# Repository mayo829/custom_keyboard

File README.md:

# Customized keyboard from scratch!

## Requirements
| Device | Requirement Met | Part number |
| LCD display | 0 |
| knob | 0 |
| [rgb backlit](https://www.digikey.com/en/products/detail/sparkfun-electronics/COM-24837/22321085?gclsrc=aw.ds&gad_source=1&gad_campaignid=20228387720&gbraid=0AAAAADrbLlgSjTrdEqANFxgXgC02mKwfv&gclid=CjwKCAiAjojLBhAlEiwAcjhrDpL0sVmSf_AmglqLysg8uP9_rsrsxjCyNCUdnPwnI6o1eOr4FKzDCRoCRfgQAvD_BwE) | 0 | COM-24837 |
| addressable rgb key lighting | 0 |
| somehow layout the normal 60% plus pgup, pgdn, del, arrows, lcd, and knob and find compatible keycaps (60% keyboard with one extra column) | 0 |
| keycaps need to be, shine-through, square, | 0 |
| case and other stuff to house the keyboard nicely | 0 |
| usbc | 0 |

## BOM
- Mcus:
   - [STM32](https://www.digikey.com/en/products/detail/stmicroelectronics/STM32F072RBT6/4815291s)

- OLED display:
   - [display]()

- Encoder:
   - [encoder](https://www.digikey.com/en/products/detail/bourns-inc/PEC11R-4315K-S0024/7314924)
   - [knob](https://www.digikey.com/en/products/detail/adafruit-industries-llc/5527/16653407?_gl=1*14h9xmt*_up*MQ..*_gs*MQ..&gclid=CjwKCAiA64LLBhBhEiwA-Pxgu-WK6Ms8d8zmGBIC-p0rfidxNpsL_D1lqFmqEvRYpyIKef8caDuRshoCzbMQAvD_BwE&gclsrc=aw.ds&gbraid=0AAAAADrbLljtQo4yarHhxgiW1udqx9cSJ)

- Keycaps
  - [165 key white, grey, red](https://www.aliexpress.us/item/3256803996803052.html?spm=a2g0o.productlist.main.35.295c494elcphuO&algo_pvid=000affab-dda6-4964-b599-618a03716f18&algo_exp_id=000affab-dda6-4964-b599-618a03716f18-34&pdp_ext_f=%7B%22order%22%3A%227%22%2C%22eval%22%3A%221%22%2C%22fromPage%22%3A%22search%22%7D&pdp_npi=6%40dis%21USD%2122.47%2115.73%21%21%2122.47%2115.73%21%402101dedf17680063575245652ec256%2112000053180571953%21sea%21US%217007458592%21X%211%210%21n_tag%3A-29911%3Bd%3Aaca9a7da%3Bm03_new_user%3A-29895&curPageLogUid=Rr0sefmQfAht&utparam-url=scene%3Asearch%7Cquery_from%3A%7Cx_object_id%3A1005004183117804%7C_p_origin_prod%3A)
  - [correct cool colors](https://www.aliexpress.us/item/3256809279540220.html?spm=a2g0o.productlist.main.55.4482ywm5ywm55W&algo_pvid=47f9f85e-3a12-452a-b59a-b0dd7382a6c9&algo_exp_id=47f9f85e-3a12-452a-b59a-b0dd7382a6c9-54&pdp_ext_f=%7B%22order%22%3A%2240%22%2C%22eval%22%3A%221%22%2C%22fromPage%22%3A%22search%22%7D&pdp_npi=6%40dis%21USD%2129.61%2120.73%21%21%21205.47%21143.83%21%402103129f17680065638523771e0064%2112000049189558375%21sea%21US%217007458592%21X%211%210%21n_tag%3A-29911%3Bd%3Aaca9a7da%3Bm03_new_user%3A-29895&curPageLogUid=t9W4kYhWIKt3&utparam-url=scene%3Asearch%7Cquery_from%3A%7Cx_object_id%3A1005009465854972%7C_p_origin_prod%3A)
  
- Switches
  - [Cherry MX2A Silent Red](https://mechanicalkeyboards.com/products/cherry-mx2a-silent-red-45g-linear?variant=48014625145132)

## Resources
- [good guide](https://github.com/ruiqimao/keyboard-pcb-guide)
- [community for keyboard designs](https://kbatelier.org/)
- [reference tutorial](https://www.youtube.com/watch?v=u13yRbBiRYM)

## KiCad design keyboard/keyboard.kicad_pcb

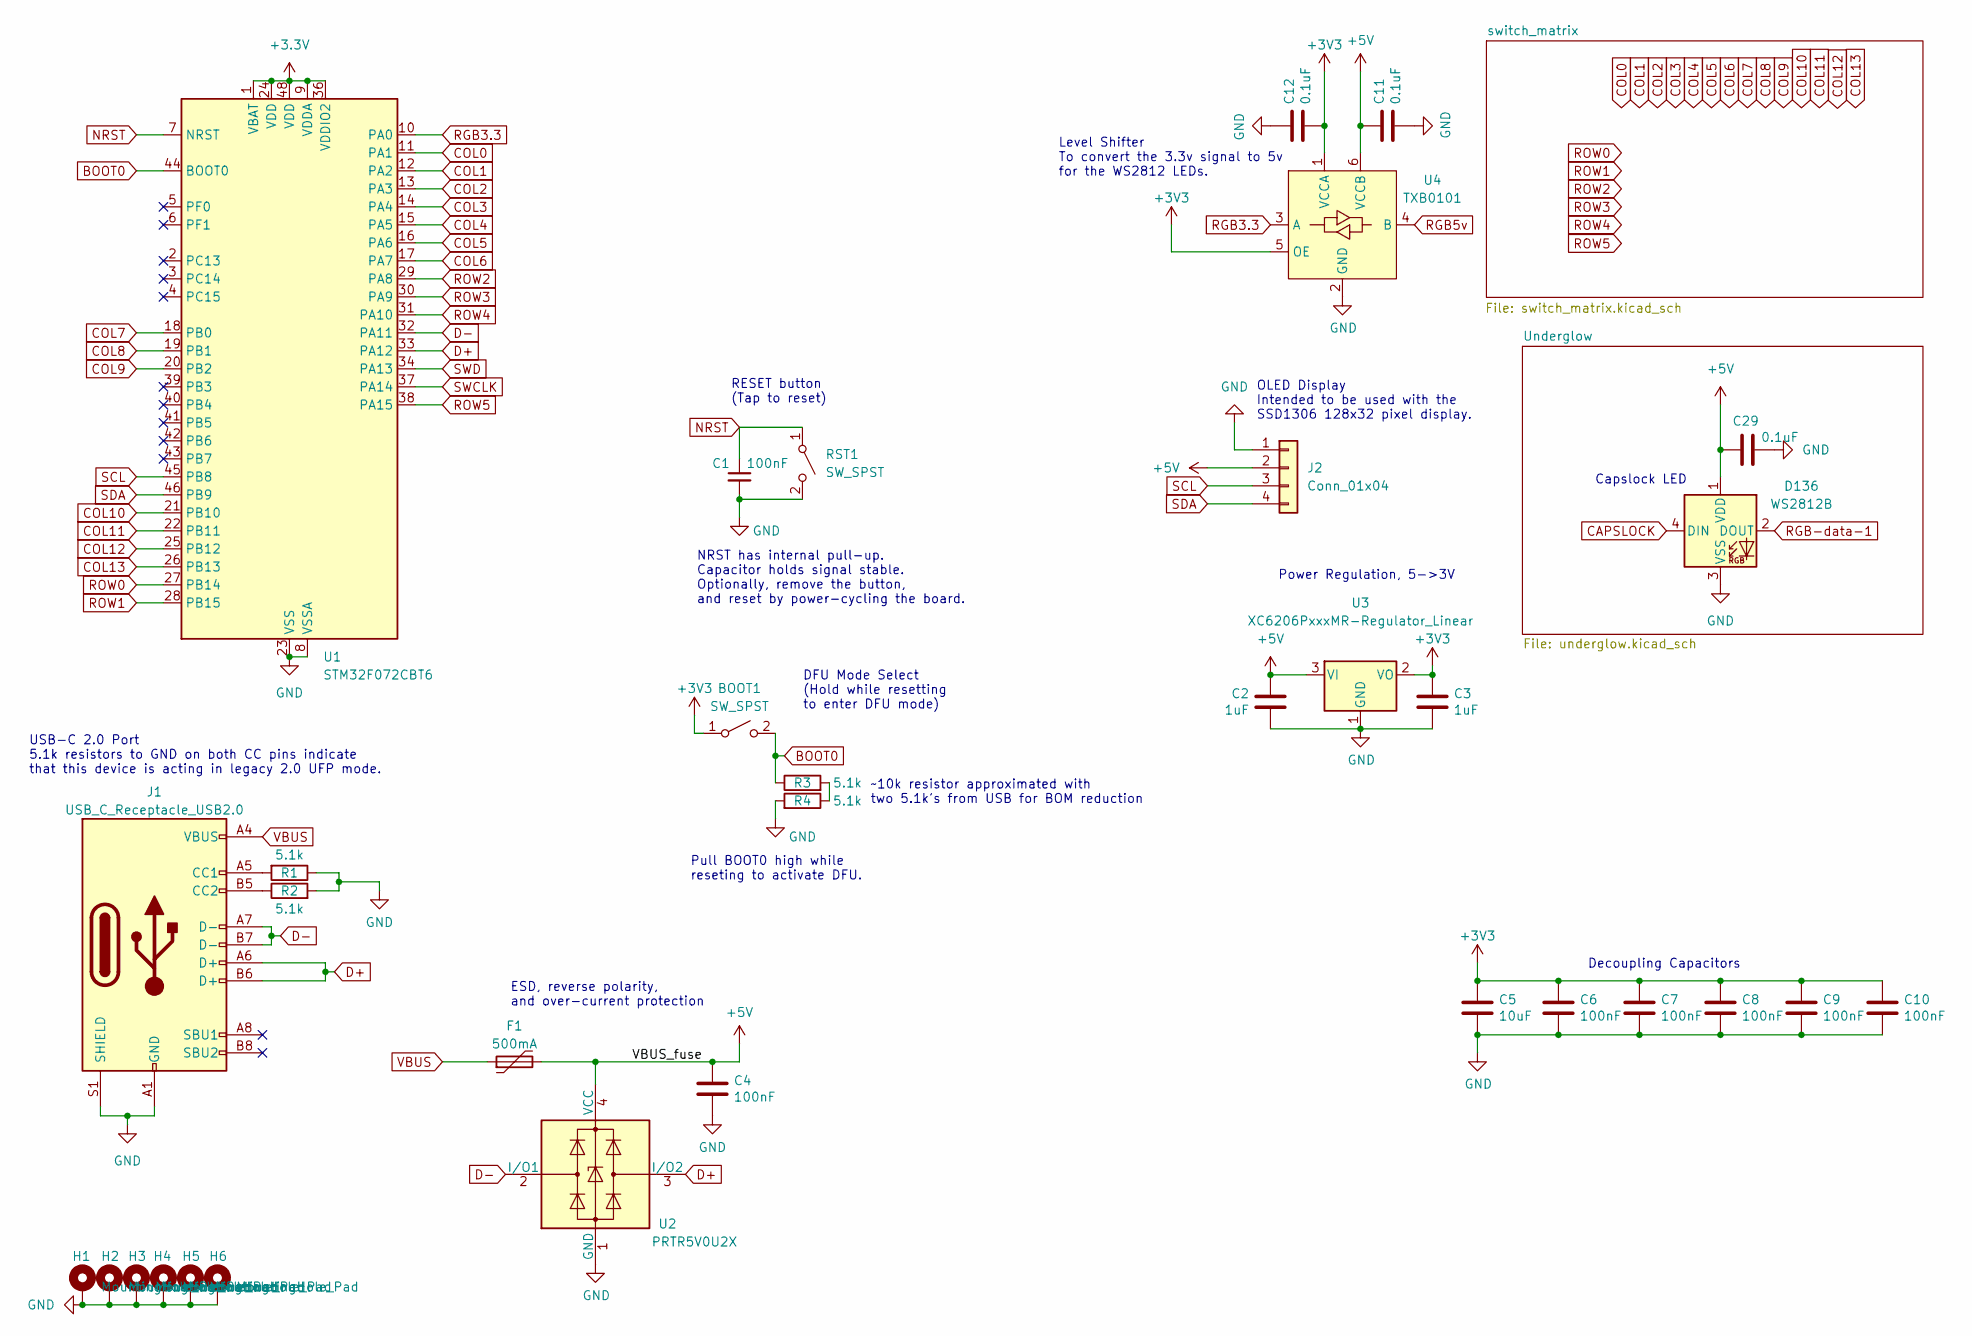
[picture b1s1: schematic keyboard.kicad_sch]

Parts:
BOOT1: SW_SPST; SW_SPST_TL3342
C1, C4, C6, C7, C8, C9, C10: 100nF; C_0402_1005Metric; LCSC C307331
C2, C3: 1uF; C_0402_1005Metric; LCSC C307331
C5: 10uF; C_0603_1608Metric; LCSC C307331
C11, C12: 0.1uF; C_0402_1005Metric; LCSC C307331
C29: 0.1uF; C_0402_1005Metric
D136: WS2812B; LED_WS2812B_PLCC4_5.0x5.0mm_P3.2mm
F1: 500mA; Fuse_1206_3216Metric; LCSC C135341
H1, H2, H3, H4, H5, H6: MountingHole_Pad; MountingHole_3.2mm_M3
J1: USB_C_Receptacle_USB2.0; USB_C_Receptacle_HRO_TYPE-C-31-M-14; JlcRotOffset 180
J2: Conn_01x04; SSD1306-0.91-OLED-4pin-128x32
R1, R2, R3, R4: 5.1k; R_0402_1005Metric
RST1: SW_SPST; SW_SPST_TL3342
U1: STM32F072CBT6; LQFP-48_7x7mm_P0.5mm
U2: PRTR5V0U2X; SOT-143; LCSC C2827688
U3: XC6206PxxxMR-Regulator_Linear; SOT-23; LCSC C5446
U4: TXB0101; SOT-363_SC-70-6_Handsoldering; LCSC C324081

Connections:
+3.3V: U1.1 (VBAT), U1.9 (VDDA), U1.24 (VDD), U1.36 (VDDIO2), U1.48 (VDD)
+3V3: BOOT1.1 (A), C3.1, C5.1, C6.1, C7.1, C8.1, C9.1, C10.1, C12.2, U3.2 (VO), U4.1 (VCCA), U4.5 (OE)
+5V: C2.1, C4.1, C11.1, C29.1, D136.1 (VDD), F1.2, J2.2, U2.4 (VCC), U3.3 (VI), U4.6 (VCCB); also elsewhere on the board
BOOT0: BOOT1.2 (B), R3.1, U1.44 (BOOT0)
CAPSLOCK: D136.4 (DIN); also elsewhere on the board
COL0: U1.11 (PA1); also elsewhere on the board
COL1: U1.12 (PA2); also elsewhere on the board
COL2: U1.13 (PA3); also elsewhere on the board
COL3: U1.14 (PA4); also elsewhere on the board
COL4: U1.15 (PA5); also elsewhere on the board
COL5: U1.16 (PA6); also elsewhere on the board
COL6: U1.17 (PA7); also elsewhere on the board
COL7: U1.18 (PB0); also elsewhere on the board
COL8: U1.19 (PB1); also elsewhere on the board
COL9: U1.20 (PB2); also elsewhere on the board
COL10: U1.21 (PB10); also elsewhere on the board
COL11: U1.22 (PB11); also elsewhere on the board
COL12: U1.25 (PB12); also elsewhere on the board
COL13: U1.26 (PB13); also elsewhere on the board
D+: J1.A6 (D+), J1.B6 (D+), U1.33 (PA12), U2.3 (I/O2)
D-: J1.A7 (D-), J1.B7 (D-), U1.32 (PA11), U2.2 (I/O1)
GND: C1.2, C2.2, C3.2, C4.2, C5.2, C6.2, C7.2, C8.2, C9.2, C10.2, C11.2, C12.1, C29.2, D136.3 (VSS), H1.1, H2.1, H3.1, H4.1, H5.1, H6.1, J1.A1 (GND), J1.A12 (GND), J1.B1 (GND), J1.B12 (GND), J1.S1 (SHIELD), J2.1, R1.1, R2.2, R4.2, RST1.2 (B), U1.8 (VSSA), U1.23 (VSS), U1.35 (VSS), U1.47 (VSS), U2.1 (GND), U3.1 (GND), U4.2 (GND); also elsewhere on the board
NRST: C1.1, RST1.1 (A), U1.7 (NRST)
unnamed: J1.A5 (CC1), R1.2
unnamed: J1.B5 (CC2), R2.1
unnamed: R3.2, R4.1
RGB3.3: U1.10 (PA0), U4.3 (A)
RGB5v: U4.4 (B); also elsewhere on the board
RGB-data-1: D136.2 (DOUT); also elsewhere on the board
ROW0: U1.27 (PB14); also elsewhere on the board
ROW1: U1.28 (PB15); also elsewhere on the board
ROW2: U1.29 (PA8); also elsewhere on the board
ROW3: U1.30 (PA9); also elsewhere on the board
ROW4: U1.31 (PA10); also elsewhere on the board
ROW5: U1.38 (PA15); also elsewhere on the board
SCL: J2.3, U1.45 (PB8)
SDA: J2.4, U1.46 (PB9)
SWCLK: U1.37 (PA14)
SWD: U1.34 (PA13)
VBUS: F1.1, J1.A4 (VBUS), J1.A9 (VBUS), J1.B4 (VBUS), J1.B9 (VBUS)

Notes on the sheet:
Decoupling Capacitors
~10k resistor approximated with two 5.1k's from USB for BOM reduction
RESET button (Tap to reset)
Power Regulation, 5->3V
Pull BOOT0 high while reseting to activate DFU.
Capslock LED
USB-C 2.0 Port 5.1k resistors to GND on both CC pins indicate that this device is acting in legacy 2.0 UFP mode.
NRST has internal pull-up. Capacitor holds signal stable. Optionally, remove the button, and reset by power-cycling the board.
ESD, reverse polarity, and over-current protection
Level Shifter To convert the 3.3v signal to 5v for the WS2812 LEDs.
OLED Display Intended to be used with the SSD1306 128x32 pixel display.
DFU Mode Select (Hold while resetting to enter DFU mode)

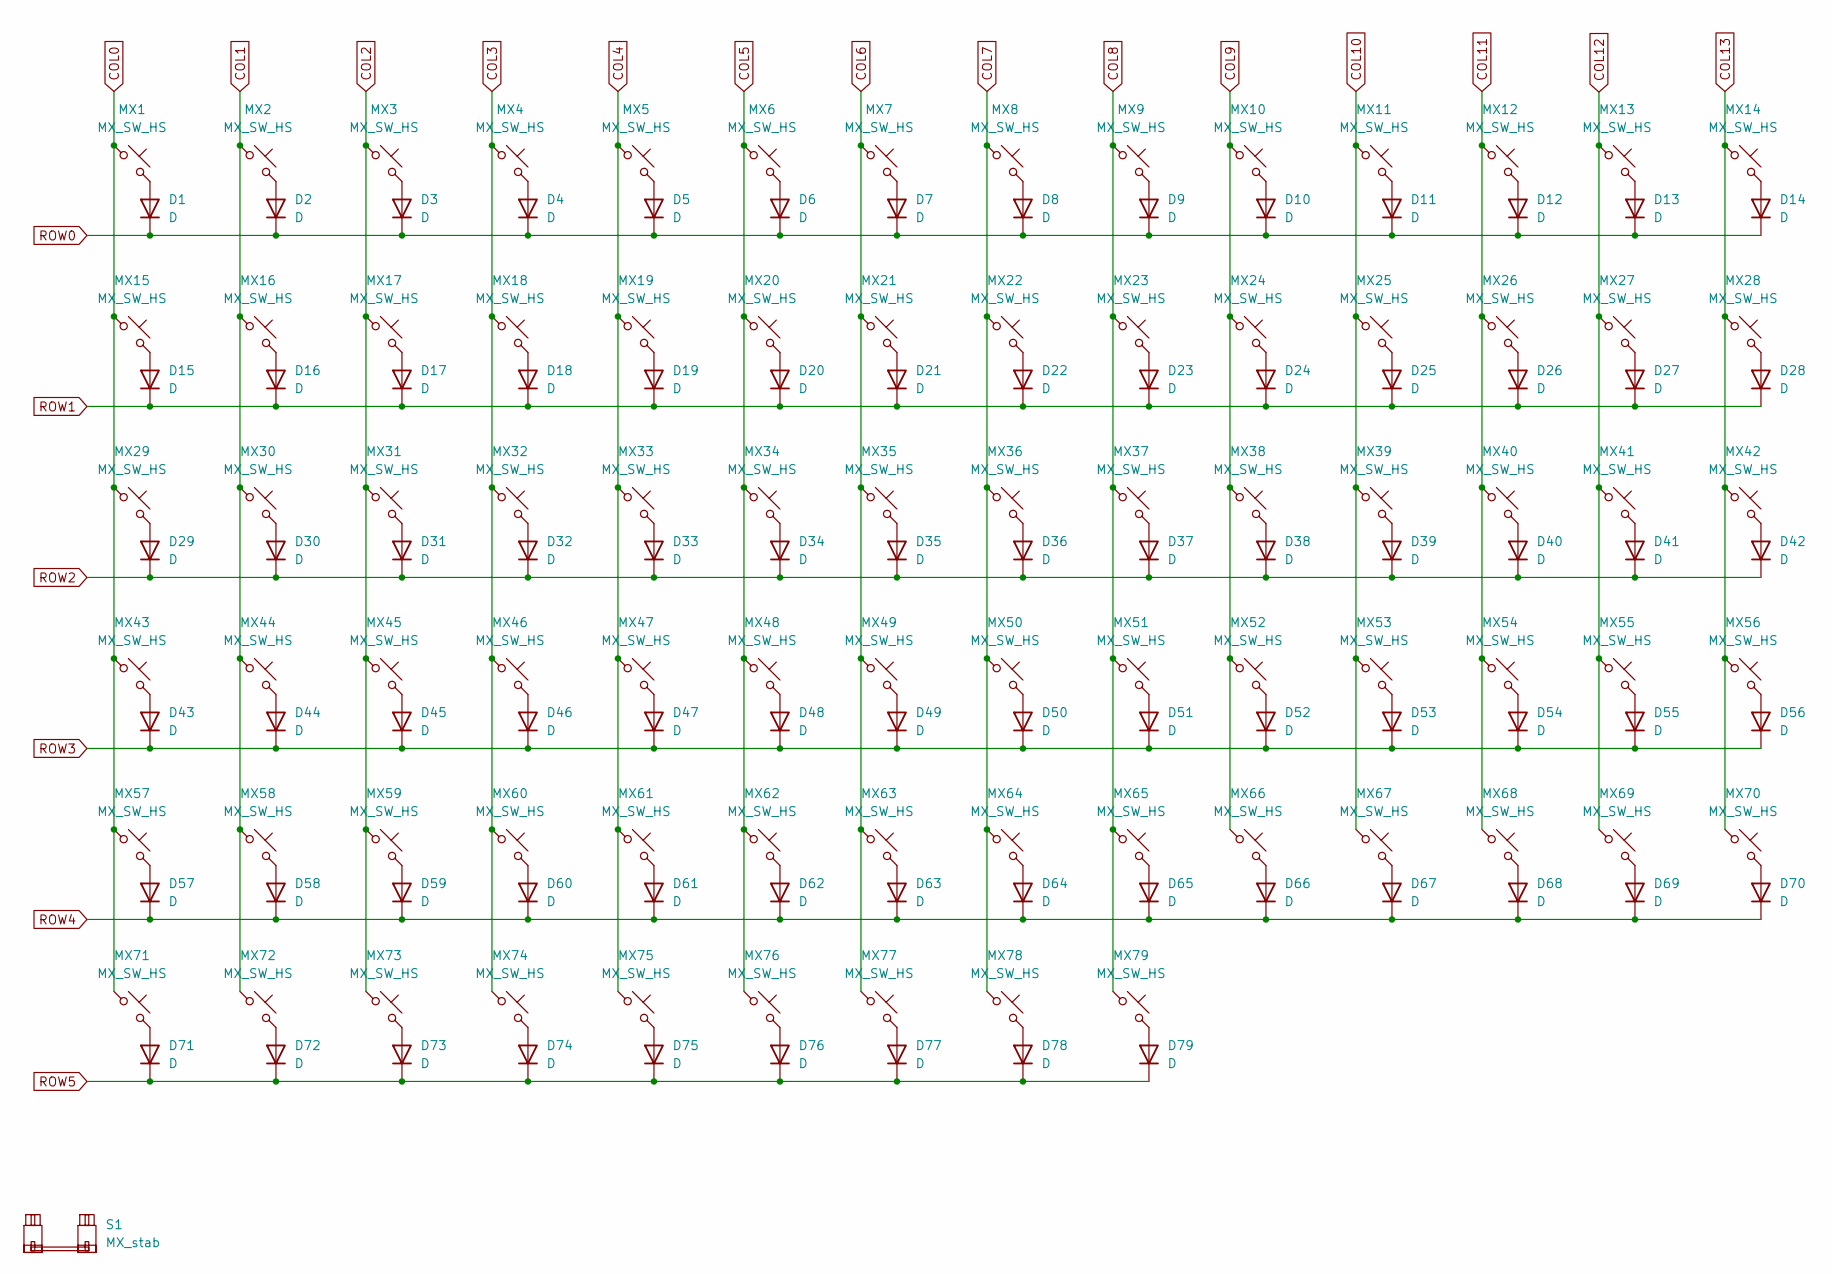
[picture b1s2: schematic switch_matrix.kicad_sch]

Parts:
D1, D2, D3, D4, D5, D6, D7, D8, D9, D10, D11, D12, D13, D14, D15, D16, D17, D18, D19, D20, D21, D22, D23, D24, D25, D26, D27, D28, D29, D30, D31, D32, D33, D34, D35, D36, D37, D38, D39, D40, D41, D42, D43, D44, D45, D46, D47, D48, D49, D50, D51, D52, D53, D54, D55, D56, D57, D58, D59, D60, D61, D62, D63, D64, D65, D66, D67, D68, D69, D70, D71, D72, D73, D74, D75, D76, D77, D78, D79: D; D_SOD-123
MX1, MX2, MX3, MX4, MX5, MX6, MX7, MX8, MX9, MX10, MX11, MX12, MX13, MX14, MX15, MX16, MX17, MX18, MX19, MX20, MX21, MX22, MX23, MX24, MX25, MX26, MX27, MX28, MX29, MX30, MX31, MX32, MX33, MX34, MX35, MX36, MX37, MX38, MX39, MX40, MX41, MX42, MX43, MX44, MX45, MX46, MX47, MX48, MX49, MX50, MX51, MX52, MX53, MX54, MX55, MX56, MX57, MX58, MX59, MX60, MX61, MX62, MX63, MX64, MX65, MX66, MX67, MX68, MX69, MX70, MX71, MX72, MX73, MX74, MX75, MX76, MX77, MX78, MX79: MX_SW_HS; SW_MX_HS_CPG151101S11_1u
S1: MX_stab; STAB_MX_P_6.25u

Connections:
COL0: MX1.1, MX15.1, MX29.1, MX43.1, MX57.1, MX71.1; also elsewhere on the board
COL1: MX2.1, MX16.1, MX30.1, MX44.1, MX58.1, MX72.1; also elsewhere on the board
COL2: MX3.1, MX17.1, MX31.1, MX45.1, MX59.1, MX73.1; also elsewhere on the board
COL3: MX4.1, MX18.1, MX32.1, MX46.1, MX60.1, MX74.1; also elsewhere on the board
COL4: MX5.1, MX19.1, MX33.1, MX47.1, MX61.1, MX75.1; also elsewhere on the board
COL5: MX6.1, MX20.1, MX34.1, MX48.1, MX62.1, MX76.1; also elsewhere on the board
COL6: MX7.1, MX21.1, MX35.1, MX49.1, MX63.1, MX77.1; also elsewhere on the board
COL7: MX8.1, MX22.1, MX36.1, MX50.1, MX64.1, MX78.1; also elsewhere on the board
COL8: MX9.1, MX23.1, MX37.1, MX51.1, MX65.1, MX79.1; also elsewhere on the board
COL9: MX10.1, MX24.1, MX38.1, MX52.1, MX66.1; also elsewhere on the board
COL10: MX11.1, MX25.1, MX39.1, MX53.1, MX67.1; also elsewhere on the board
COL11: MX12.1, MX26.1, MX40.1, MX54.1, MX68.1; also elsewhere on the board
COL12: MX13.1, MX27.1, MX41.1, MX55.1, MX69.1; also elsewhere on the board
COL13: MX14.1, MX28.1, MX42.1, MX56.1, MX70.1; also elsewhere on the board
unnamed: D1.2 (A), MX1.2
unnamed: D2.2 (A), MX2.2
unnamed: D3.2 (A), MX3.2
unnamed: D4.2 (A), MX4.2
unnamed: D5.2 (A), MX5.2
unnamed: D6.2 (A), MX6.2
unnamed: D7.2 (A), MX7.2
unnamed: D8.2 (A), MX8.2
unnamed: D9.2 (A), MX9.2
unnamed: D10.2 (A), MX10.2
unnamed: D11.2 (A), MX11.2
unnamed: D12.2 (A), MX12.2
unnamed: D13.2 (A), MX13.2
unnamed: D14.2 (A), MX14.2
unnamed: D15.2 (A), MX15.2
unnamed: D16.2 (A), MX16.2
unnamed: D17.2 (A), MX17.2
unnamed: D18.2 (A), MX18.2
unnamed: D19.2 (A), MX19.2
unnamed: D20.2 (A), MX20.2
unnamed: D21.2 (A), MX21.2
unnamed: D22.2 (A), MX22.2
unnamed: D23.2 (A), MX23.2
unnamed: D24.2 (A), MX24.2
unnamed: D25.2 (A), MX25.2
unnamed: D26.2 (A), MX26.2
unnamed: D27.2 (A), MX27.2
unnamed: D28.2 (A), MX28.2
unnamed: D29.2 (A), MX29.2
unnamed: D30.2 (A), MX30.2
unnamed: D31.2 (A), MX31.2
unnamed: D32.2 (A), MX32.2
unnamed: D33.2 (A), MX33.2
unnamed: D34.2 (A), MX34.2
unnamed: D35.2 (A), MX35.2
unnamed: D36.2 (A), MX36.2
unnamed: D37.2 (A), MX37.2
unnamed: D38.2 (A), MX38.2
unnamed: D39.2 (A), MX39.2
unnamed: D40.2 (A), MX40.2
unnamed: D41.2 (A), MX41.2
unnamed: D42.2 (A), MX42.2
unnamed: D43.2 (A), MX43.2
unnamed: D44.2 (A), MX44.2
unnamed: D45.2 (A), MX45.2
unnamed: D46.2 (A), MX46.2
unnamed: D47.2 (A), MX47.2
unnamed: D48.2 (A), MX48.2
unnamed: D49.2 (A), MX49.2
unnamed: D50.2 (A), MX50.2
unnamed: D51.2 (A), MX51.2
unnamed: D52.2 (A), MX52.2
unnamed: D53.2 (A), MX53.2
unnamed: D54.2 (A), MX54.2
unnamed: D55.2 (A), MX55.2
unnamed: D56.2 (A), MX56.2
unnamed: D57.2 (A), MX57.2
unnamed: D58.2 (A), MX58.2
unnamed: D59.2 (A), MX59.2
unnamed: D60.2 (A), MX60.2
unnamed: D61.2 (A), MX61.2
unnamed: D62.2 (A), MX62.2
unnamed: D63.2 (A), MX63.2
unnamed: D64.2 (A), MX64.2
unnamed: D65.2 (A), MX65.2
unnamed: D66.2 (A), MX66.2
unnamed: D67.2 (A), MX67.2
unnamed: D68.2 (A), MX68.2
unnamed: D69.2 (A), MX69.2
unnamed: D70.2 (A), MX70.2
unnamed: D71.2 (A), MX71.2
unnamed: D72.2 (A), MX72.2
unnamed: D73.2 (A), MX73.2
unnamed: D74.2 (A), MX74.2
unnamed: D75.2 (A), MX75.2
unnamed: D76.2 (A), MX76.2
unnamed: D77.2 (A), MX77.2
unnamed: D78.2 (A), MX78.2
unnamed: D79.2 (A), MX79.2
ROW0: D1.1 (K), D2.1 (K), D3.1 (K), D4.1 (K), D5.1 (K), D6.1 (K), D7.1 (K), D8.1 (K), D9.1 (K), D10.1 (K), D11.1 (K), D12.1 (K), D13.1 (K), D14.1 (K); also elsewhere on the board
ROW1: D15.1 (K), D16.1 (K), D17.1 (K), D18.1 (K), D19.1 (K), D20.1 (K), D21.1 (K), D22.1 (K), D23.1 (K), D24.1 (K), D25.1 (K), D26.1 (K), D27.1 (K), D28.1 (K); also elsewhere on the board
ROW2: D29.1 (K), D30.1 (K), D31.1 (K), D32.1 (K), D33.1 (K), D34.1 (K), D35.1 (K), D36.1 (K), D37.1 (K), D38.1 (K), D39.1 (K), D40.1 (K), D41.1 (K), D42.1 (K); also elsewhere on the board
ROW3: D43.1 (K), D44.1 (K), D45.1 (K), D46.1 (K), D47.1 (K), D48.1 (K), D49.1 (K), D50.1 (K), D51.1 (K), D52.1 (K), D53.1 (K), D54.1 (K), D55.1 (K), D56.1 (K); also elsewhere on the board
ROW4: D57.1 (K), D58.1 (K), D59.1 (K), D60.1 (K), D61.1 (K), D62.1 (K), D63.1 (K), D64.1 (K), D65.1 (K), D66.1 (K), D67.1 (K), D68.1 (K), D69.1 (K), D70.1 (K); also elsewhere on the board
ROW5: D71.1 (K), D72.1 (K), D73.1 (K), D74.1 (K), D75.1 (K), D76.1 (K), D77.1 (K), D78.1 (K), D79.1 (K); also elsewhere on the board

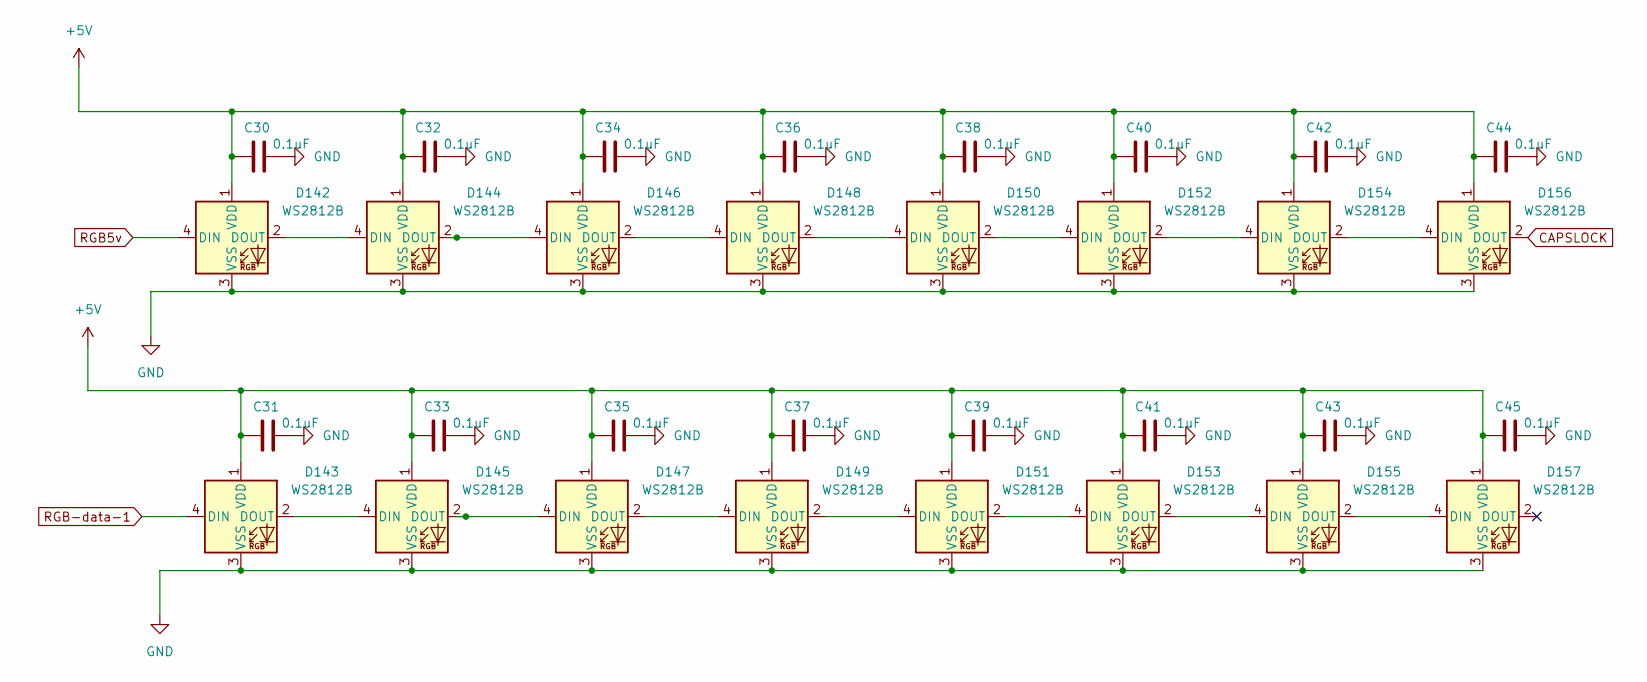
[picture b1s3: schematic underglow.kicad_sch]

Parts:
C30, C31, C32, C33, C34, C35, C36, C37, C38, C39, C40, C41, C42, C43, C44, C45: 0.1uF; C_0402_1005Metric
D142, D143, D144, D145, D146, D147, D148, D149, D150, D151, D152, D153, D154, D155, D156, D157: WS2812B; LED_WS2812B_PLCC4_5.0x5.0mm_P3.2mm

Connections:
+5V: C30.1, C31.1, C32.1, C33.1, C34.1, C35.1, C36.1, C37.1, C38.1, C39.1, C40.1, C41.1, C42.1, C43.1, C44.1, C45.1, D142.1 (VDD), D143.1 (VDD), D144.1 (VDD), D145.1 (VDD), D146.1 (VDD), D147.1 (VDD), D148.1 (VDD), D149.1 (VDD), D150.1 (VDD), D151.1 (VDD), D152.1 (VDD), D153.1 (VDD), D154.1 (VDD), D155.1 (VDD), D156.1 (VDD), D157.1 (VDD); also elsewhere on the board
CAPSLOCK: D156.2 (DOUT); also elsewhere on the board
GND: C30.2, C31.2, C32.2, C33.2, C34.2, C35.2, C36.2, C37.2, C38.2, C39.2, C40.2, C41.2, C42.2, C43.2, C44.2, C45.2, D142.3 (VSS), D143.3 (VSS), D144.3 (VSS), D145.3 (VSS), D146.3 (VSS), D147.3 (VSS), D148.3 (VSS), D149.3 (VSS), D150.3 (VSS), D151.3 (VSS), D152.3 (VSS), D153.3 (VSS), D154.3 (VSS), D155.3 (VSS), D156.3 (VSS), D157.3 (VSS); also elsewhere on the board
unnamed: D142.2 (DOUT), D144.4 (DIN)
unnamed: D143.2 (DOUT), D145.4 (DIN)
unnamed: D144.2 (DOUT), D146.4 (DIN)
unnamed: D145.2 (DOUT), D147.4 (DIN)
unnamed: D146.2 (DOUT), D148.4 (DIN)
unnamed: D147.2 (DOUT), D149.4 (DIN)
unnamed: D148.2 (DOUT), D150.4 (DIN)
unnamed: D149.2 (DOUT), D151.4 (DIN)
unnamed: D150.2 (DOUT), D152.4 (DIN)
unnamed: D151.2 (DOUT), D153.4 (DIN)
unnamed: D152.2 (DOUT), D154.4 (DIN)
unnamed: D153.2 (DOUT), D155.4 (DIN)
unnamed: D154.2 (DOUT), D156.4 (DIN)
unnamed: D155.2 (DOUT), D157.4 (DIN)
RGB5v: D142.4 (DIN); also elsewhere on the board
RGB-data-1: D143.4 (DIN); also elsewhere on the board

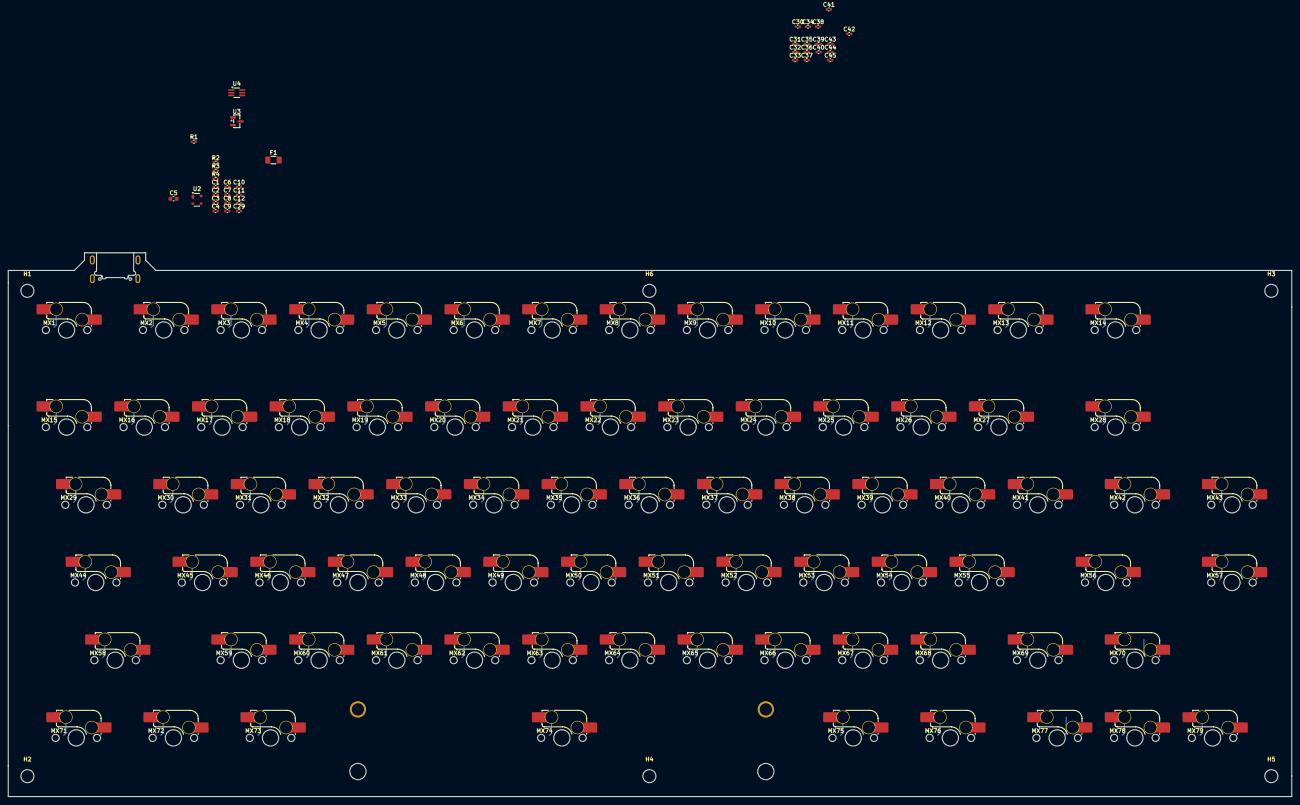
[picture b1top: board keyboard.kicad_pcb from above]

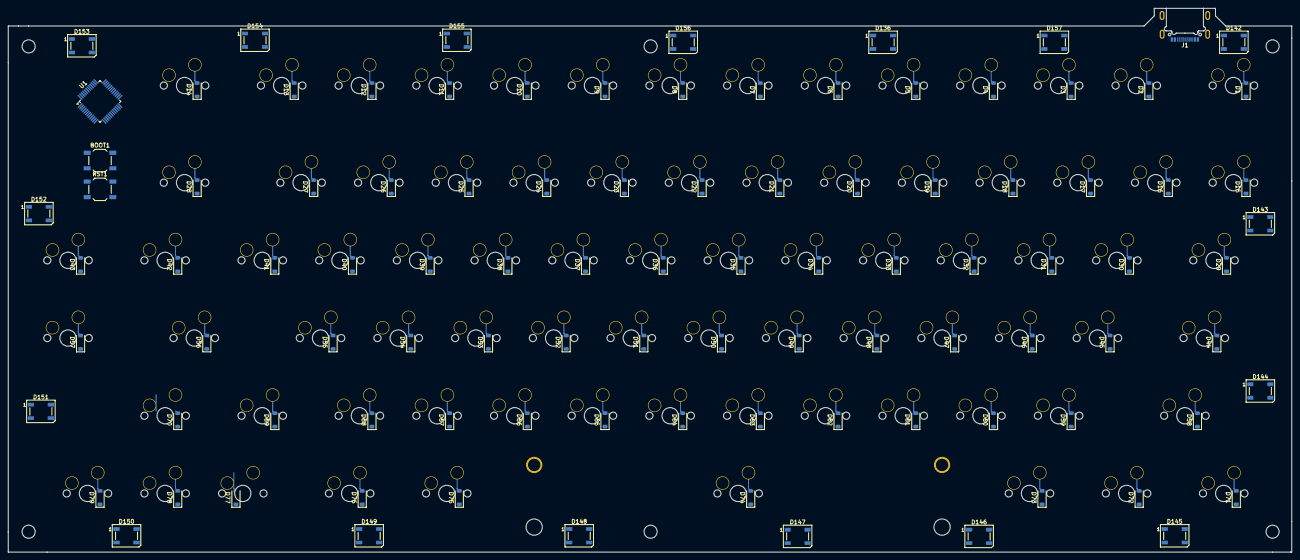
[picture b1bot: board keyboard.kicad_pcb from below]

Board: 2 copper layers, 314.7 x 133.3 mm, 223 parts (100 on the bottom side), 129 nets.

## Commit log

2026-01-09 resources and BOM
2026-01-09 auto push
2026-01-09 Fix formatting in README for BOM and Resources sections
